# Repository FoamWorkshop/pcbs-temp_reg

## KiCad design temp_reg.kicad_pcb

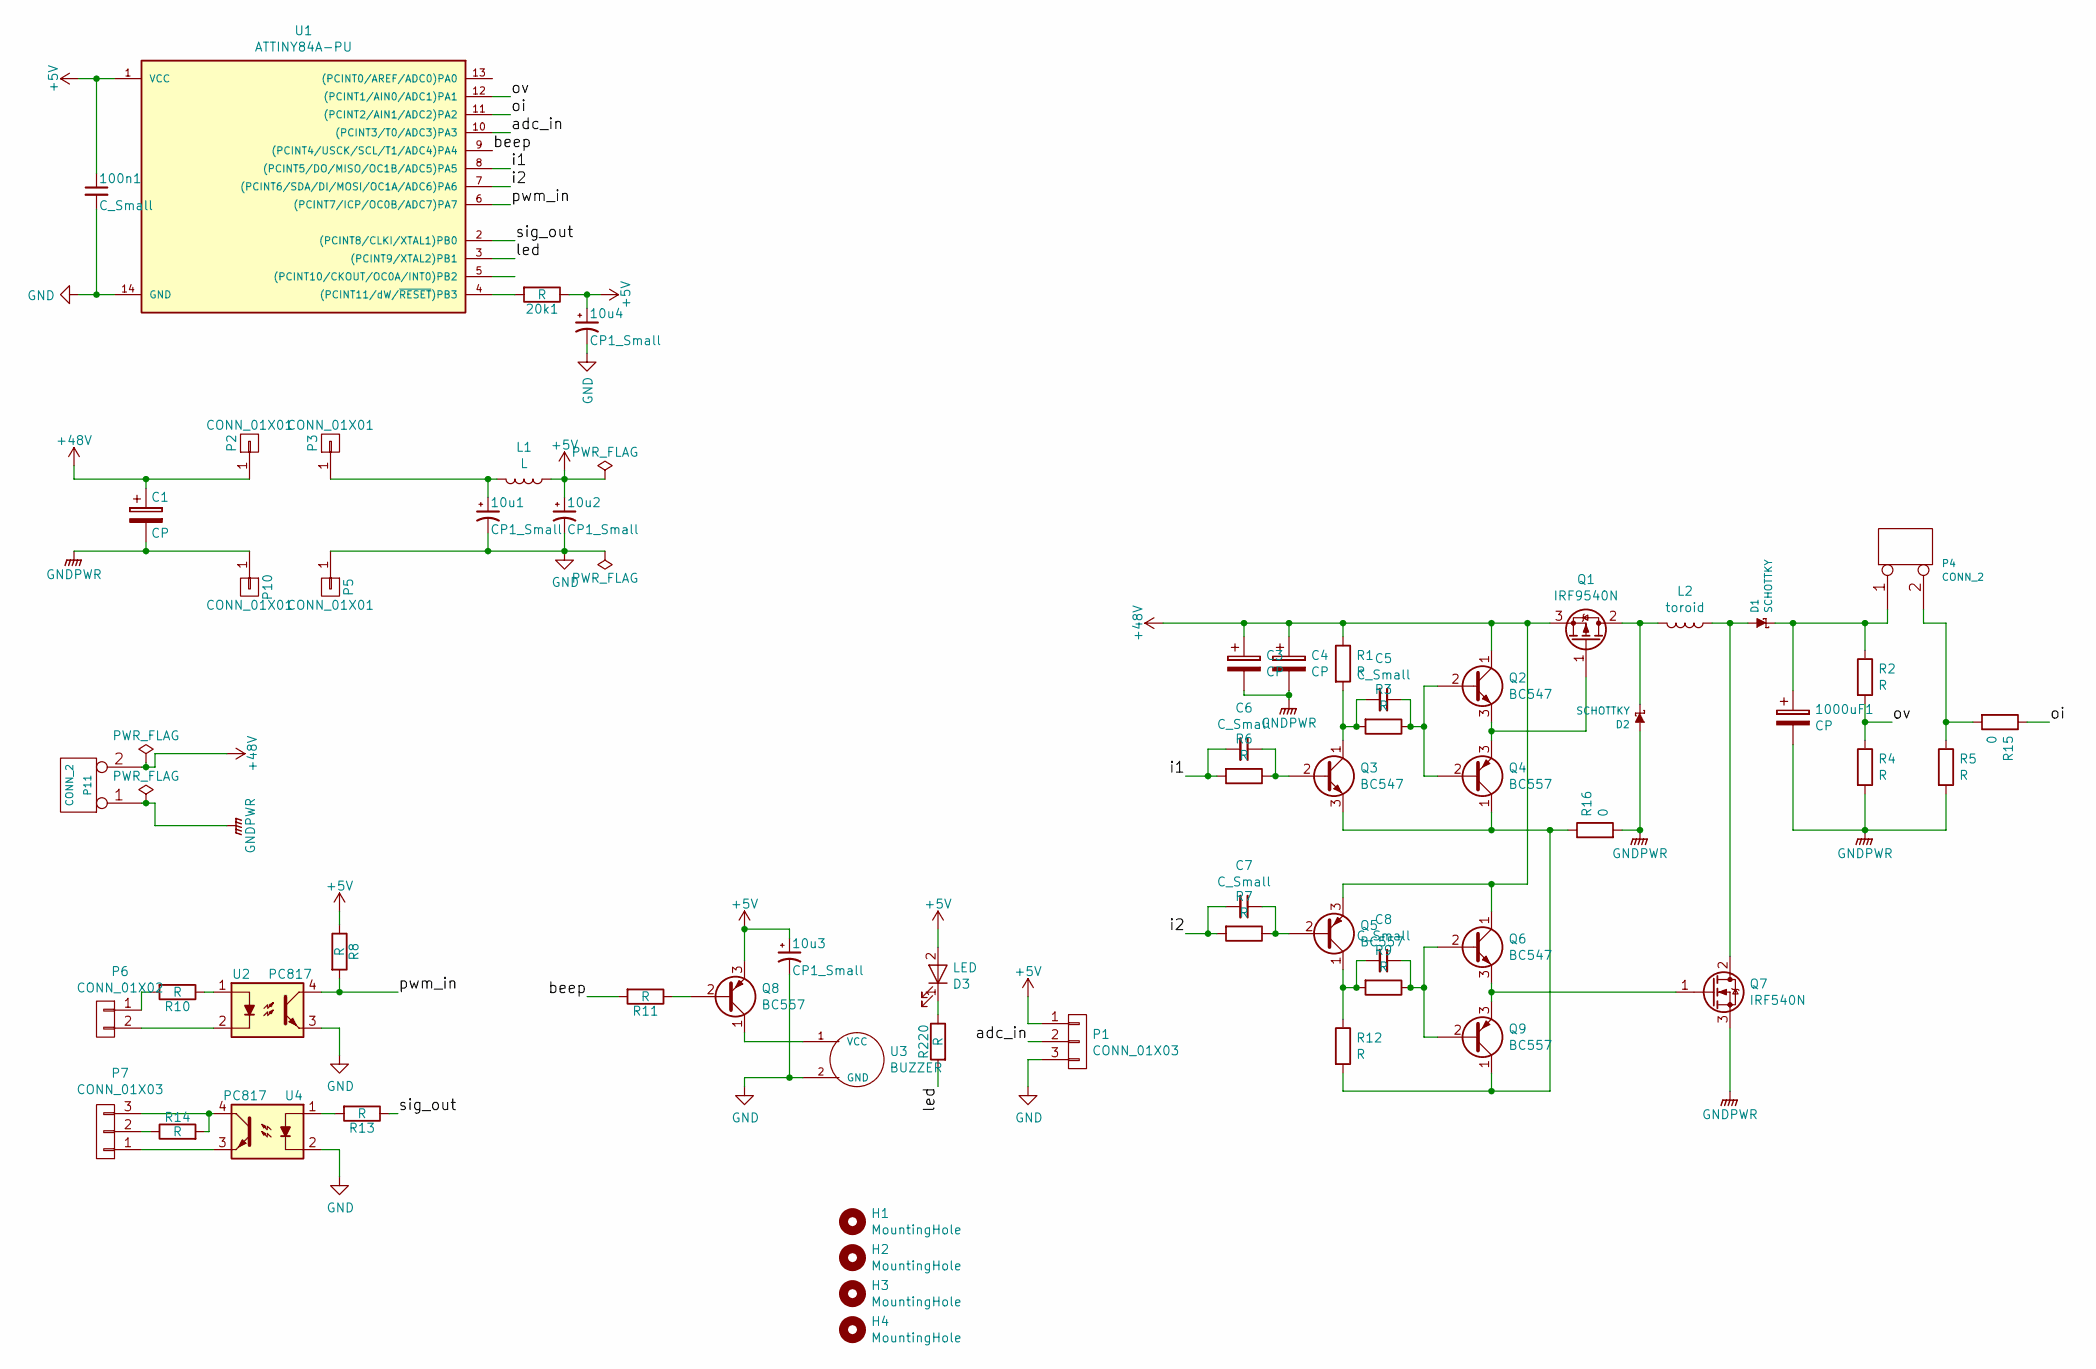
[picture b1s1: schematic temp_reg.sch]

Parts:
10u1, 10u2, 10u3, 10u4: CP1_Small; CP_Radial_D5.0mm_P2.50mm
20k1: R; R_Axial_DIN0207_L6.3mm_D2.5mm_P10.16mm_Horizontal
100n1: C_Small; C_Disc_D3.0mm_W1.6mm_P2.50mm
1000uF1: CP; CP_Radial_D25.0mm_P10.00mm_SnapIn
C1: CP; CP_Radial_D10.0mm_P5.00mm
C3: CP; CP_Radial_D25.0mm_P10.00mm_SnapIn
C4: CP; CP_Radial_D7.5mm_P2.50mm
C5, C7, C8: C_Small; C_Disc_D4.3mm_W1.9mm_P5.00mm
C6: C_Small; R_Axial_DIN0207_L6.3mm_D2.5mm_P10.16mm_Horizontal
D1, D2: SCHOTTKY; D_A-405_P12.70mm_Horizontal
D3: LED; LED_D4.0mm
H1, H2, H3, H4: MountingHole; MountingHole_3.2mm_M3
L1: L; L_Axial_L5.3mm_D2.2mm_P7.62mm_Horizontal_Vishay_IM-1
L2: toroid; L_Toroid_Vertical_L21.6mm_W9.5mm_P7.11mm_Pulse_C
P1, P7: CONN_01X03; Pin_Header_Straight_1x03_Pitch2.54mm
P2, P3, P5, P10: CONN_01X01; Pin_Header_Straight_1x01_Pitch2.54mm
P4, P11: CONN_2; bornier2_V
P6: CONN_01X02; Pin_Header_Straight_1x02_Pitch2.54mm
Q1: IRF9540N; TO-220-3_Vertical
Q2, Q3, Q6: BC547; TO-92_Inline_Wide
Q4, Q5, Q8, Q9: BC557; TO-92_Inline_Wide
Q7: IRF540N; TO-220-3_Vertical
R1, R2, R3, R4, R5, R6, R7, R8, R9, R10, R11, R12, R13, R14, R220: R; R_Axial_DIN0207_L6.3mm_D2.5mm_P10.16mm_Horizontal
R15, R16: 0; R_Axial_DIN0207_L6.3mm_D2.5mm_P10.16mm_Horizontal
U1: ATTINY84A-PU; DIP-14_W7.62mm_Socket_LongPads
U2, U4: PC817; DIP-4_W7.62mm_LongPads
U3: BUZZER; Buzzer_12x9.5RM7.6

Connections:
+5V: 10u2.1, 10u3.1, 10u4.1, 20k1.1, 100n1.1, D3.2 (A), L1.1, P1.1, Q8.3 (E), R8.1, U1.1 (VCC)
+48V: C1.1, C3.1, C4.1, P2.1, P11.2, Q1.3 (S), Q2.1 (C), Q5.3 (E), Q6.1 (C), R1.1
/adc_in: P1.2, U1.10 ((PCINT3/T0/ADC3)PA3)
/beep: R11.2, U1.9 ((PCINT4/USCK/SCL/T1/ADC4)PA4)
/i1: C6.2, R6.2, U1.8 ((PCINT5/DO/MISO/OC1B/ADC5)PA5)
/i2: C7.2, R7.2, U1.7 ((PCINT6/SDA/DI/MOSI/OC1A/ADC6)PA6)
/led: R220.2, U1.3 ((PCINT9/XTAL2)PB1)
/oi: R15.1, U1.11 ((PCINT2/AIN1/ADC2)PA2)
/ov: R2.2, R4.1, U1.12 ((PCINT1/AIN0/ADC1)PA1)
/pwm_in: R8.2, U1.6 ((PCINT7/ICP/OC0B/ADC7)PA7), U2.4
/sig_out: R13.1, U1.2 ((PCINT8/CLKI/XTAL1)PB0)
GND: 10u1.2, 10u2.2, 10u3.2, 10u4.2, 100n1.2, P1.3, P5.1, U1.14 (GND), U2.3, U3.2 (GND), U4.2
unnamed: 10u1.1, L1.2, P3.1
unnamed: 20k1.2, U1.4 ((PCINT11/dW/~RESET~)PB3)
unnamed: 1000uF1.1, D1.2 (K), P4.1, R2.1
unnamed: C5.1, Q2.2 (B), Q4.2 (B), R3.1
unnamed: C5.2, Q3.1 (C), R1.2, R3.2
unnamed: C6.1, Q3.2 (B), R6.1
unnamed: C7.1, Q5.2 (B), R7.1
unnamed: C8.1, Q6.2 (B), Q9.2 (B), R9.1
unnamed: C8.2, Q5.1 (C), R9.2, R12.1
unnamed: D1.1 (A), L2.1, Q7.2 (D)
unnamed: D2.2 (K), L2.2, Q1.2 (D)
unnamed: D3.1 (K), R220.1
unnamed: P4.2, R5.1, R15.2
unnamed: P6.1, R10.2
unnamed: P6.2, U2.2
unnamed: P7.1, U4.3
unnamed: P7.2, R14.1
unnamed: P7.3, R14.2, U4.4
unnamed: Q1.1 (G), Q2.3 (E), Q4.3 (E)
unnamed: Q6.3 (E), Q7.1 (G), Q9.3 (E)
unnamed: Q8.1 (C), U3.1 (VCC)
unnamed: Q8.2 (B), R11.1
unnamed: R10.1, U2.1
unnamed: R13.2, U4.1

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
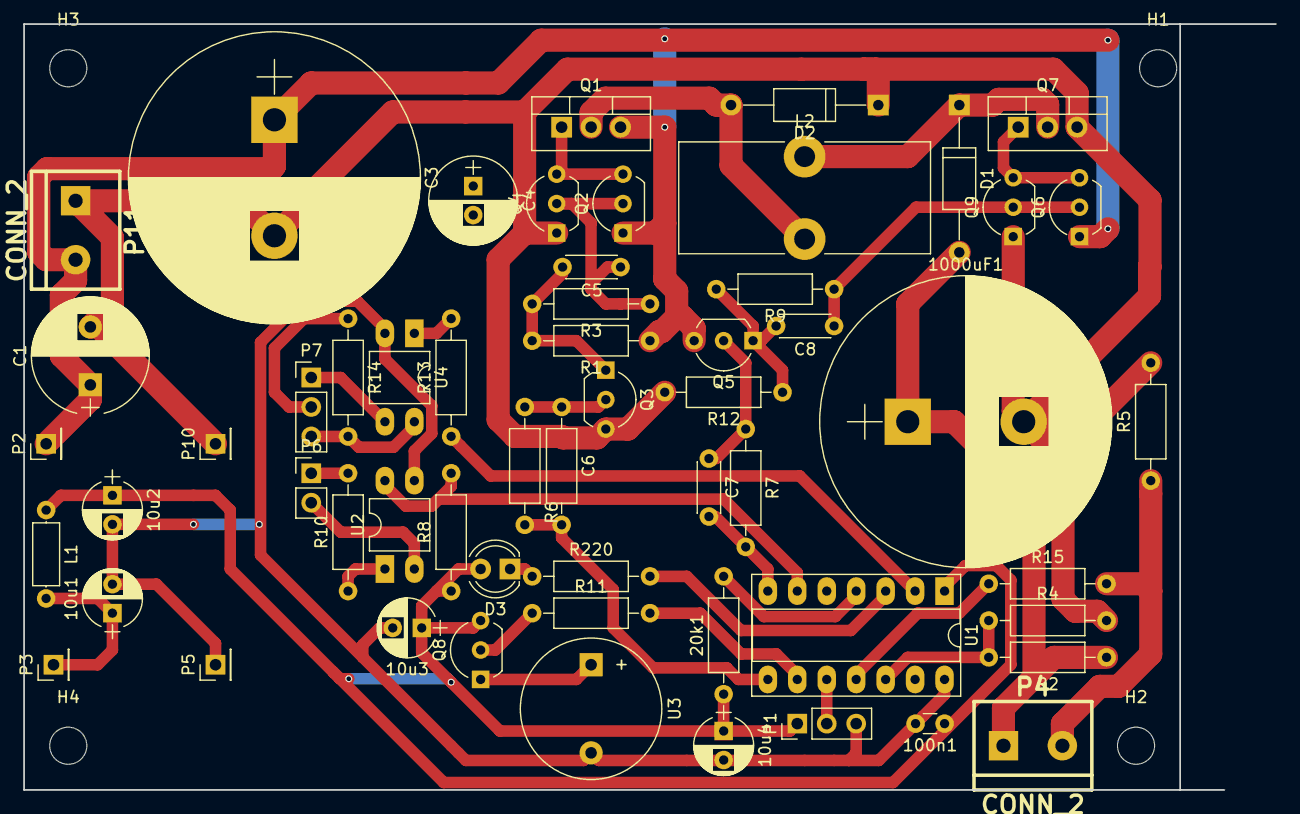
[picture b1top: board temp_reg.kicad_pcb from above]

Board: 2 copper layers, 107.9 x 66.0 mm, 61 parts (0 on the bottom side), 37 nets.

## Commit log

2016-09-08 complete beeper
2016-09-09 added regulator
2016-09-13 encoder+Vref
2016-09-13 2ADC
2016-09-21 start reducing number of components
2016-09-26 milestone version
2017-03-16 boost converter version
2017-09-19 change to power opamp
2017-10-06 change to modular architecture
2017-12-11 circuit built
2017-12-11 changed current sensing method, added lm358, lm7812, icl7660
2018-06-13 before merge
2018-06-17 finished pcbart
2018-11-01 working version
